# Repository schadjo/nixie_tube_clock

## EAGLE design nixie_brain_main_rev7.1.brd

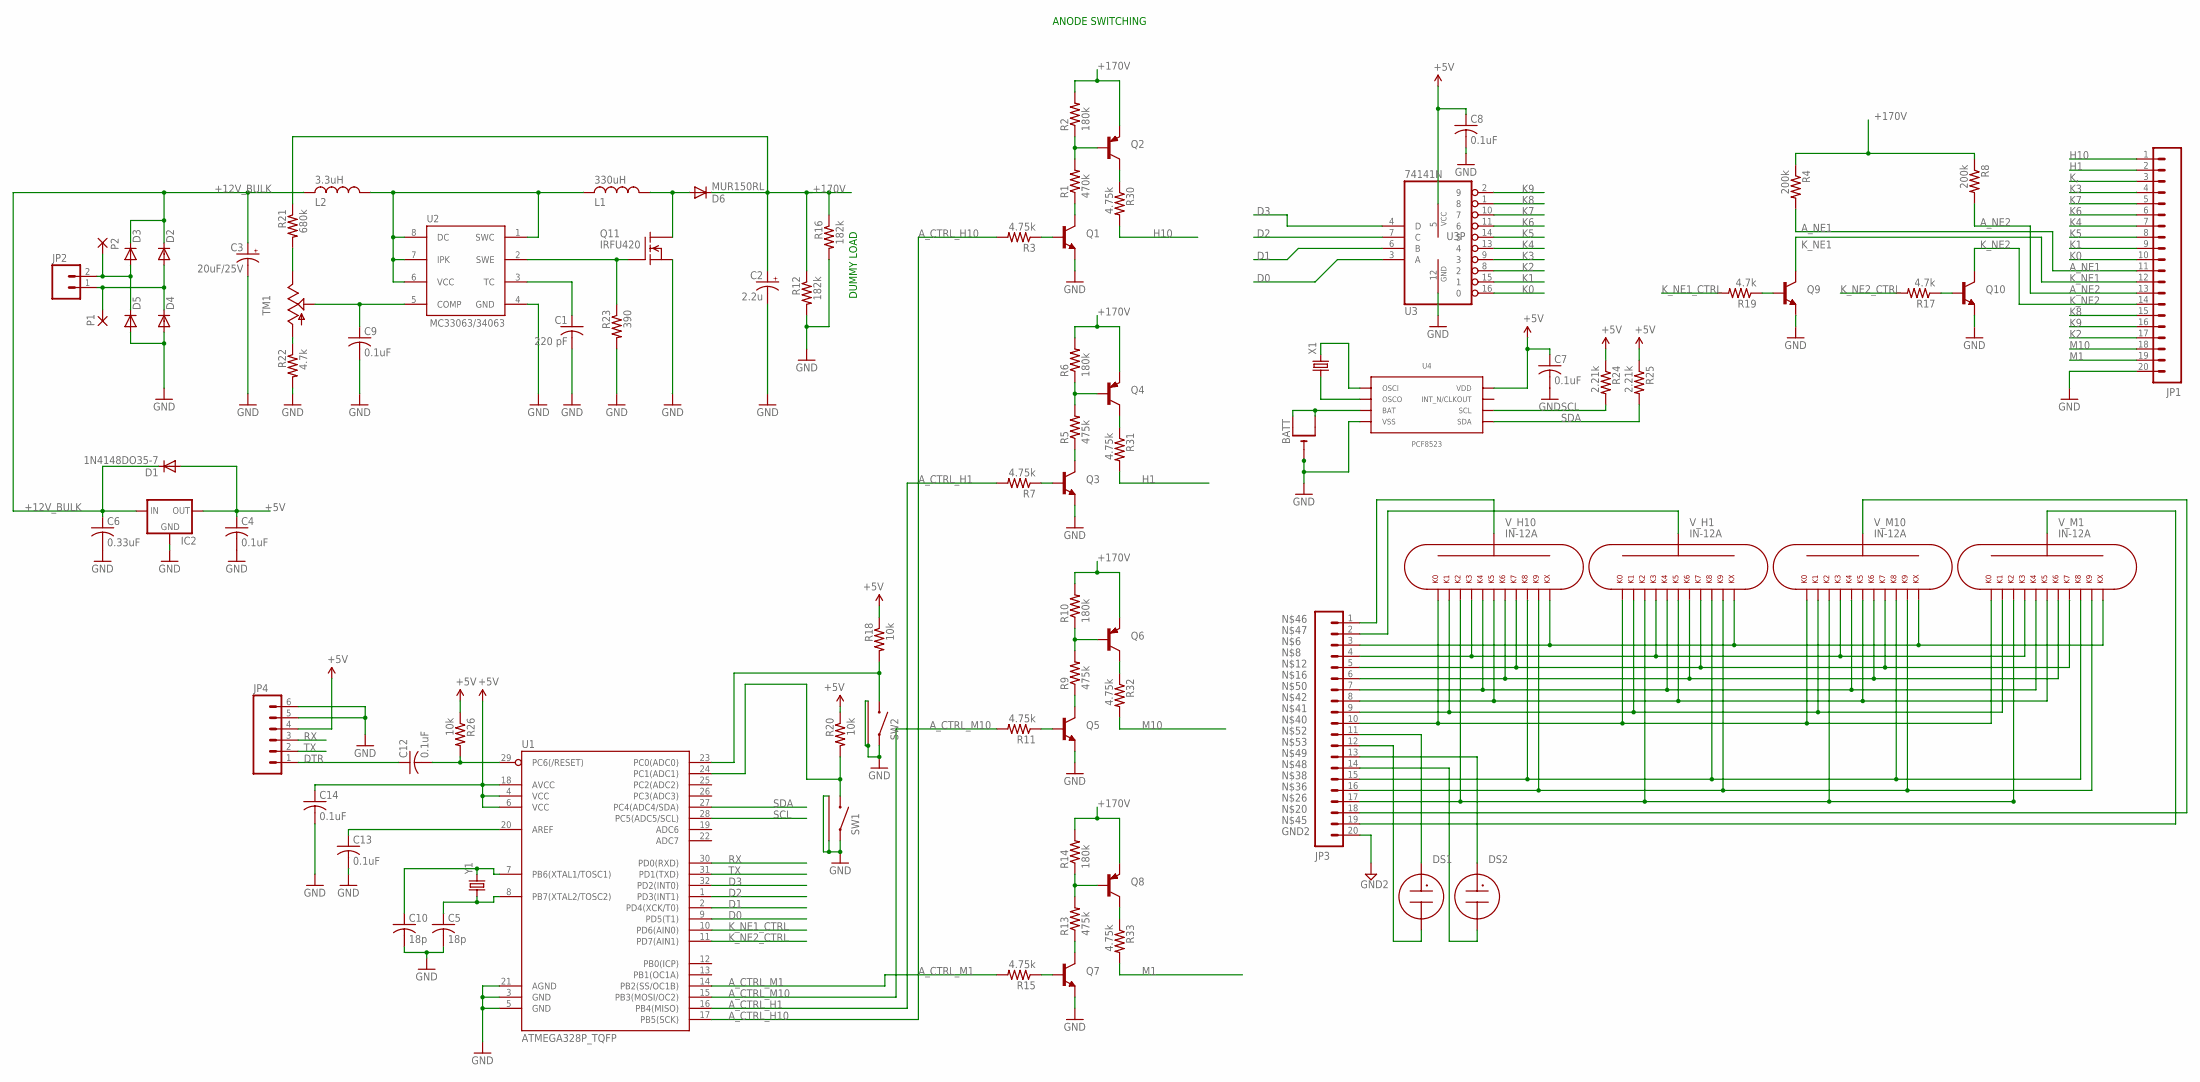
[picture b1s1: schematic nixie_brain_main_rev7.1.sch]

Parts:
BATT: CR1220SMT; CR1220-SMD
C1: 220 pF; C025-025X050
C2: 2.2u; E5-8,5
C3: 20uF/25V; E2,5-5
C4, C7, C8, C9, C12, C13, C14: 0.1uF; C025-025X050
C5, C10: 18p; C1206
C6: 0.33uF; C025-025X050
D1: 1N4148DO35-7; DO35-7
D2, D3, D4, D5: DIODE1N4148; DIODE-1N4148
D6: MUR150RL; DO41-10
DS1, DS2: NE-2
IC2: V_REG_78XXSINK; TO220-IGO
JP1, JP3: M20LOCK; 1X20_LOCK
JP2: M02LOCK; 1X02_LOCK
JP4: M06LOCK; 1X06_LOCK
L1: 330uH; 22R334C
L2: 3.3uH; 11R332C
P1, P2: WIREPAD2,15/1,0; 2,15/1,0
Q1, Q3, Q5, Q7, Q9, Q10: MPSA42-NPN-TO92-EBC; TO92-EBC
Q2, Q4, Q6, Q8: MPSA92-PNP-TO92-EBC; TO92-EBC
Q11: IRFU420
R1: 470k; R1206
R2, R6, R10, R14: 180k; R1206
R3, R7, R11, R15, R30, R31, R32, R33: 4.75k; R1206
R4, R8: 200k; R1206
R5, R9, R13: 475k; R1206
R12, R16: 182k; R1206
R17, R19, R22: 4.7k; R1206
R18, R20, R26: 10k; R1206
R21: 680k; R1206
R23: 390; R1206
R24, R25: 2.21k; R1206
SW1, SW2: CT1102V5-85F100
TM1: TRIM; 6MM
U1: ATMEGA328P_TQFP; TQFP32-08
U2: MC33063/MC34063P; DIL08
U3: 74141N; DIL16
U4: PCF8523
V_H1, V_H10: IN-12A
V_M1, V_M10: IN-12A
X1: MC-306
Y1: CRYSTAL5X3; CRYSTAL-SMD-5X3

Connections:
+5V: C4.1, C7.1, C8.1, C14.1, D1.A, IC2.OUT, JP4.4, R18.1, R20.1, R24.1, R25.1, R26.1, U1.4 (VCC), U1.6 (VCC), U1.18 (AVCC), U3.5 (VCC), U4.8 (P8_VDD)
+12V_BULK: C3.+, C6.1, D1.C, D2.C, D3.C, IC2.IN, L2.P$2 (2)
+170V: C2.+, D6.C, Q2.E, Q4.E, Q6.E, Q8.E, R2.2, R4.1, R6.2, R8.1, R10.2, R12.1, R14.2, R16.1, R21.1
A_CTRL_H1: R7.2, U1.16 (PB4(MISO))
A_CTRL_H10: R3.2, U1.17 (PB5(SCK))
A_CTRL_M1: R15.2, U1.14 (PB2(SS/OC1B))
A_CTRL_M10: R11.2, U1.15 (PB3(MOSI/OC2))
A_NE1: JP1.11, R4.2
A_NE2: JP1.13, R8.2
D0: U1.9 (PD5(T1)), U3.3 (A)
D1: U1.2 (PD4(XCK/T0)), U3.6 (B)
D2: U1.1 (PD3(INT1)), U3.7 (C)
D3: U1.32 (PD2(INT0)), U3.4 (D)
DTR: C12.1, JP4.1
GND: BATT.-, C1.2, C2.-, C3.-, C4.2, C5.2, C6.2, C7.2, C8.2, C9.2, C10.2, C13.2, C14.2, D4.A, D5.A, IC2.GND, JP1.20, JP4.5, JP4.6, Q1.E, Q3.E, Q5.E, Q7.E, Q9.E, Q10.E, Q11.S, R12.2, R16.2, R22.2, R23.2, SW1.P1_SW, SW1.P$3 (P3_CHASSIS), SW1.P$4 (P4_CHASSIS), SW2.P1_SW, SW2.P$3 (P3_CHASSIS), SW2.P$4 (P4_CHASSIS), U1.3 (GND), U1.5 (GND), U1.21 (AGND), U2.4 (GND), U3.12 (GND), U4.4 (P4_VSS)
GND2: JP3.20
H1: JP1.2, R31.2
H10: JP1.1, R30.2
K0: JP1.10, U3.16 (0)
K1: JP1.9, U3.15 (1)
K2: JP1.17, U3.8 (2)
K3: JP1.4, U3.9 (3)
K4: JP1.7, U3.13 (4)
K5: JP1.8, U3.14 (5)
K6: JP1.6, U3.11 (6)
K7: JP1.5, U3.10 (7)
K8: JP1.15, U3.1 (8)
K9: JP1.16, U3.2 (9)
K,: JP1.3
K_NE1: JP1.12, Q9.C
K_NE1_CTRL: R19.2, U1.10 (PD6(AIN0))
K_NE2: JP1.14, Q10.C
K_NE2_CTRL: R17.2, U1.11 (PD7(AIN1))
M1: JP1.19, R33.2
M10: JP1.18, R32.2
unnamed: Q2.B, R1.2, R2.1
unnamed: Q1.C, R1.1
unnamed: Q1.B, R3.1
unnamed: Q4.B, R5.2, R6.1
unnamed: Q3.C, R5.1
unnamed: JP3.3, V_H1.P12_KX (NC), V_H10.P12_KX (NC), V_M1.P12_KX (NC), V_M10.P12_KX (NC)
unnamed: Q3.B, R7.1
unnamed: JP3.4, V_H1.P9_K3 (K3), V_H10.P9_K3 (K3), V_M1.P9_K3 (K3), V_M10.P9_K3 (K3)
unnamed: Q6.B, R9.2, R10.1
unnamed: Q5.C, R9.1
unnamed: Q5.B, R11.1
unnamed: JP3.5, V_H1.P5_K7 (K7), V_H10.P5_K7 (K7), V_M1.P5_K7 (K7), V_M10.P5_K7 (K7)
unnamed: Q8.B, R13.2, R14.1
unnamed: Q7.C, R13.1
unnamed: Q7.B, R15.1
unnamed: JP3.6, V_H1.P6_K6 (K6), V_H10.P6_K6 (K6), V_M1.P6_K6 (K6), V_M10.P6_K6 (K6)
unnamed: R18.2, SW2.P2_SW, U1.23 (PC0(ADC0))
unnamed: R20.2, SW1.P2_SW, U1.24 (PC1(ADC1))
unnamed: Q9.B, R19.1
unnamed: JP3.18, V_M10.P1_A (A)
unnamed: Q10.B, R17.1
unnamed: C12.2, R26.2, U1.29 (PC6(/RESET))
unnamed: U4.1 (P1_OSCI), X1.4 (2)
unnamed: U4.2 (P2_OSCO), X1.1
unnamed: BATT.+$1 (+), BATT.+$2 (+1), U4.3 (P3_BAT)
unnamed: JP3.17, V_H1.P10_K2 (K2), V_H10.P10_K2 (K2), V_M1.P10_K2 (K2), V_M10.P10_K2 (K2)
unnamed: L1.P$2 (2), L2.P$1 (1), U2.1 (SWC), U2.6 (VCC), U2.7 (IPK), U2.8 (DC)
unnamed: R21.2, TM1.E
unnamed: C9.1, TM1.S, U2.5 (COMP)
unnamed: C13.1, U1.20 (AREF)
unnamed: C1.1, U2.3 (TC)
unnamed: C10.1, U1.7 (PB6(XTAL1/TOSC1)), Y1.3 (2)
unnamed: Q11.G, R23.1, U2.2 (SWE)
unnamed: R22.1, TM1.A
unnamed: JP3.16, V_H1.P3_K9 (K9), V_H10.P3_K9 (K9), V_M1.P3_K9 (K9), V_M10.P3_K9 (K9)
unnamed: D3.A, D5.C, JP2.2, P2.1
unnamed: JP3.15, V_H1.P4_K8 (K8), V_H10.P4_K8 (K8), V_M1.P4_K8 (K8), V_M10.P4_K8 (K8)
unnamed: D2.A, D4.C, JP2.1, P1.1
unnamed: JP3.10, V_H1.P2_K0 (K0), V_H10.P2_K0 (K0), V_M1.P2_K0 (K0), V_M10.P2_K0 (K0)
unnamed: JP3.9, V_H1.P11_K1 (K1), V_H10.P11_K1 (K1), V_M1.P11_K1 (K1), V_M10.P11_K1 (K1)
unnamed: JP3.8, V_H1.P7_K5 (K5), V_H10.P7_K5 (K5), V_M1.P7_K5 (K5), V_M10.P7_K5 (K5)
unnamed: Q2.C, R30.1
unnamed: JP3.19, V_M1.P1_A (A)
unnamed: JP3.1, V_H10.P1_A (A)
unnamed: JP3.2, V_H1.P1_A (A)
unnamed: DS2.K, JP3.14
unnamed: DS2.A, JP3.13
unnamed: JP3.7, V_H1.P8_K4 (K4), V_H10.P8_K4 (K4), V_M1.P8_K4 (K4), V_M10.P8_K4 (K4)
unnamed: Q4.C, R31.1
unnamed: DS1.A, JP3.11
unnamed: DS1.K, JP3.12
unnamed: Q6.C, R32.1
unnamed: Q8.C, R33.1
unnamed: C5.1, U1.8 (PB7(XTAL2/TOSC2)), Y1.1
unnamed: D6.A, L1.P$1 (1), Q11.D, Q11.D_PAD (D)
RX: JP4.3, U1.30 (PD0(RXD))
SCL: R24.2, U1.28 (PC5(ADC5/SCL)), U4.6 (P6_SCL)
SDA: R25.2, U1.27 (PC4(ADC4/SDA)), U4.5 (P5_SDA)
TX: JP4.2, U1.31 (PD1(TXD))

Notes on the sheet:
ANODE SWITCHING
DUMMY LOAD

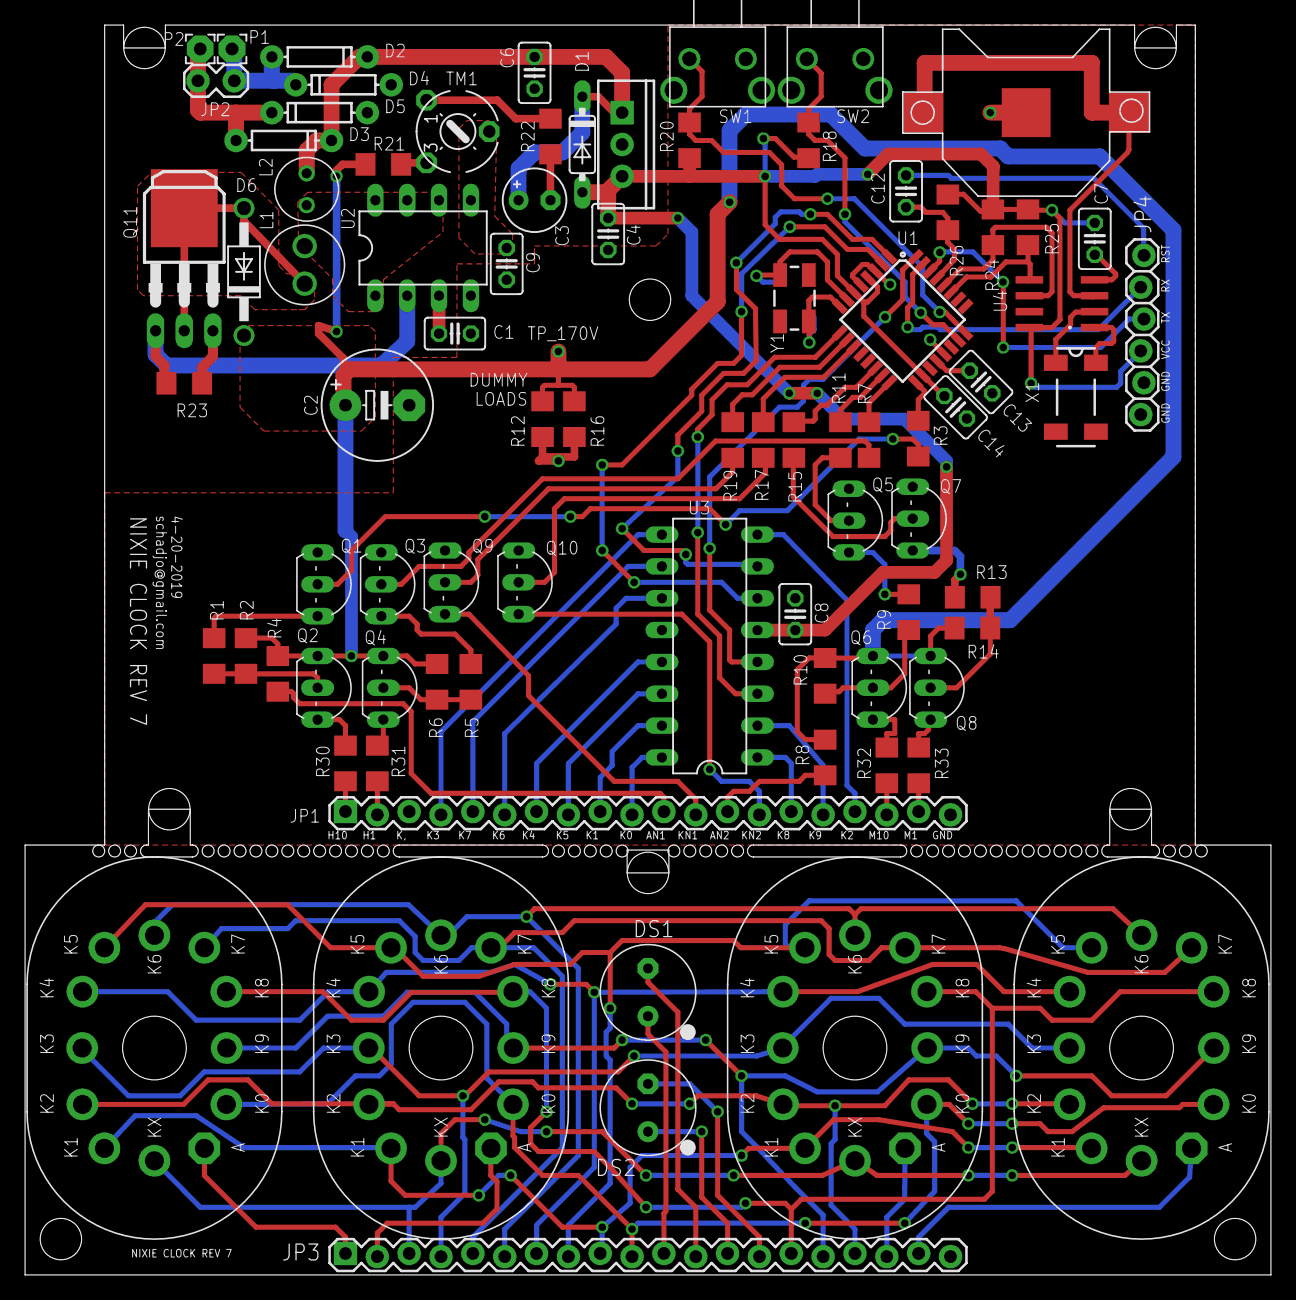
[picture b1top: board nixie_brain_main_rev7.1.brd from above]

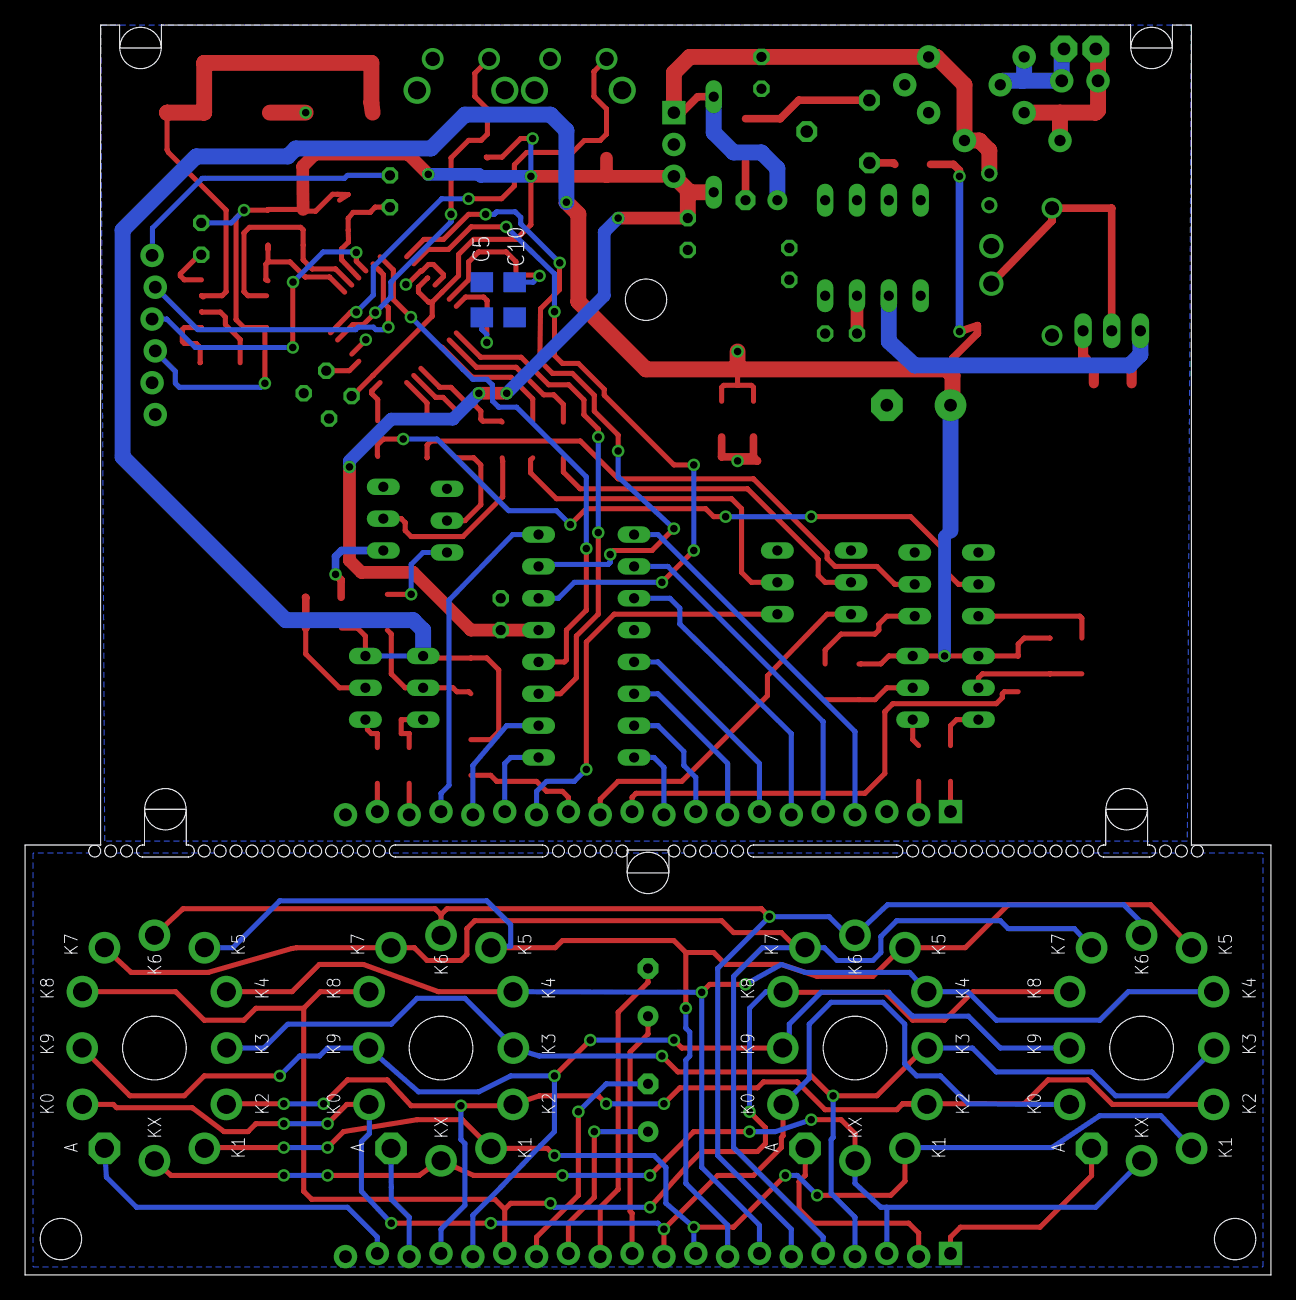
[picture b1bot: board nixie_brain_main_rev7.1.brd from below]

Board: 2 copper layers, 99.4 x 99.7 mm, 85 parts (2 on the bottom side), 92 nets.

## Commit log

2019-05-23 First commit. Swapped tx/rx pins on programming header and fixed incorrect feedback path on SMPS circuit.
2019-05-23 Added logo board file

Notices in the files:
parts and their libraries:
SparkFun: Licensing: CC v3.0 Share-Alike You are welcome to use this library for commercial purposes.
SparkFun-Connectors: Licensing: Creative Commons ShareAlike 4.0 International - https://creativecommons.org/licenses/by-sa/4.0
